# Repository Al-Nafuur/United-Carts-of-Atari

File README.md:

# Atari 2600 PlusCart

## Description
the Atari 2600 PlusCart ist based on Robin Edwards Unocart-2600 (https://github.com/robinhedwards/UnoCart-2600) and the extensions of Christian Speckner's (DirtyHairy) fork (https://github.com/DirtyHairy/UnoCart-2600). The PlusCart has no SD-Card, but an ESP8266 to connect to a local WiFi Network and the Internet.
The PlusCart downloads the ROM-files from an Server in the Internet called the "PlusStore". The way this is done is similar to the way the Unocart-2600 loads ROMs from the FAT filesystem on the SD-card, while the VCS is performing a waitroutine in his RAM.

## PlusROM
Additionally the PlusCart has one more interesting feature. It offers **internet access** to the ROM Developers, these functions are called "[PlusROM](http://pcart.firmaplus.de/pico/?PlusROM)". Examples for PlusROMs can be found in the [PlusROM-Hacks Repository](https://github.com/Al-Nafuur/PlusROM-Hacks) on Github.

## [Documentation](http://pcart.firmaplus.de/pico/)
More information and documentation can be found at the [PlusCart website](http://pcart.firmaplus.de/pico/)

Copyright:

(c) Firmaplus(+) Ltd.

Dipl.Ing.(FH) Wolfgang Stubig

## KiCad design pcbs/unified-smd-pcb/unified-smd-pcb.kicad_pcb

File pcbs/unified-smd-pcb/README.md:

Unified PlusCart UnoCart SMD PCB
===============

based on Randy Glenn's Unocart2600 PCB 
https://github.com/rglenn/unocart2600-pcb

migrated to KiCAD 6 and PlusCart WiFi module ESP8266 added by Wolfgang Stubig

Licensed under CERN OHL 1.2. See LICENSE.txt for more information.

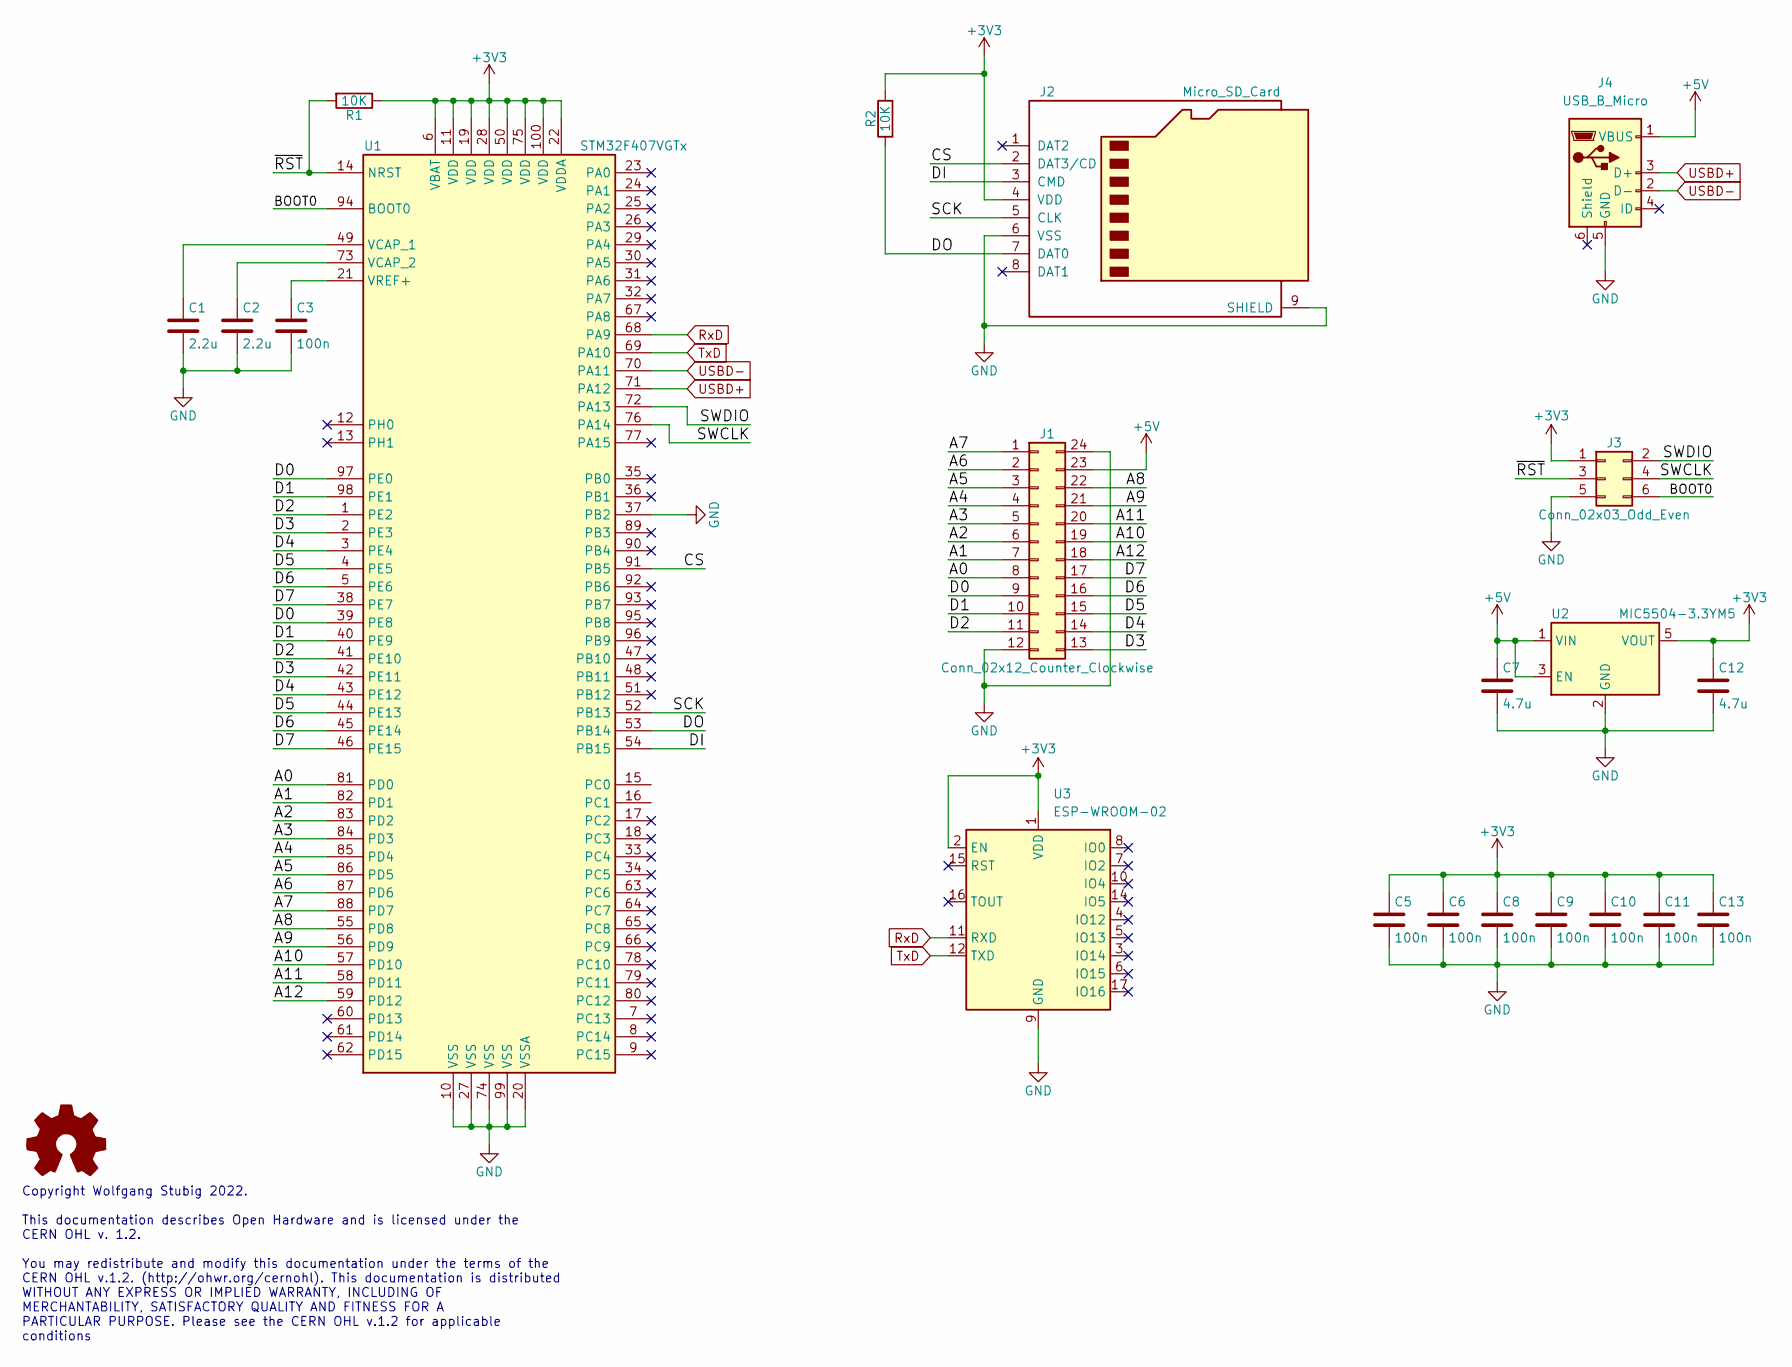
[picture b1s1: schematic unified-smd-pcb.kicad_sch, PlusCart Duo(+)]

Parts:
C1, C2: 2.2u; C_0603_1608Metric
C3, C5, C6, C8, C9, C10, C11, C13: 100n; C_0603_1608Metric
C7, C12: 4.7u; C_0805_2012Metric
J1: Conn_02x12_Counter_Clockwise; 2600-CARTRIDGE
J2: Micro_SD_Card; microSD_HRO_TF_01A
J3: Conn_02x03_Odd_Even; Tag-Connect_TC2030-IDC-NL_2x03_P1.27mm_Vertical
J4: USB_B_Micro; USB_Micro-B_Molex_47346-0001
R1, R2: 10K; R_0603_1608Metric
U1: STM32F407VGTx; LQFP-100_14x14mm_P0.5mm
U2: MIC5504-3.3YM5; SOT-23-5
U3: ESP-WROOM-02

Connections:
+3V3: C5.1, C6.1, C8.1, C9.1, C10.1, C11.1, C12.1, C13.1, J2.4 (VDD), J3.1, R1.1, R2.2, U1.6 (VBAT), U1.11 (VDD), U1.19 (VDD), U1.22 (VDDA), U1.28 (VDD), U1.50 (VDD), U1.75 (VDD), U1.100 (VDD), U2.5 (VOUT), U3.1 (VDD), U3.2 (EN)
+5V: C7.1, J1.23, J4.1 (VBUS), U2.1 (VIN), U2.3 (EN)
/A0: J1.8, U1.81 (PD0)
/A1: J1.7, U1.82 (PD1)
/A2: J1.6, U1.83 (PD2)
/A3: J1.5, U1.84 (PD3)
/A4: J1.4, U1.85 (PD4)
/A5: J1.3, U1.86 (PD5)
/A6: J1.2, U1.87 (PD6)
/A7: J1.1, U1.88 (PD7)
/A8: J1.22, U1.55 (PD8)
/A9: J1.21, U1.56 (PD9)
/A10: J1.19, U1.57 (PD10)
/A11: J1.20, U1.58 (PD11)
/A12: J1.18, U1.59 (PD12)
/BOOT0: J3.6, U1.94 (BOOT0)
/CS: J2.2 (DAT3/CD), U1.91 (PB5)
/D0: J1.9, U1.39 (PE8), U1.97 (PE0)
/D1: J1.10, U1.40 (PE9), U1.98 (PE1)
/D2: J1.11, U1.1 (PE2), U1.41 (PE10)
/D3: J1.13, U1.2 (PE3), U1.42 (PE11)
/D4: J1.14, U1.3 (PE4), U1.43 (PE12)
/D5: J1.15, U1.4 (PE5), U1.44 (PE13)
/D6: J1.16, U1.5 (PE6), U1.45 (PE14)
/D7: J1.17, U1.38 (PE7), U1.46 (PE15)
/DI: J2.3 (CMD), U1.54 (PB15)
/DO: J2.7 (DAT0), R2.1, U1.53 (PB14)
/SCK: J2.5 (CLK), U1.52 (PB13)
/SWCLK: J3.4, U1.76 (PA14)
/SWDIO: J3.2, U1.72 (PA13)
/~RST: J3.3, R1.2, U1.14 (NRST)
GND: C1.2, C2.2, C3.2, C5.2, C6.2, C7.2, C8.2, C9.2, C10.2, C11.2, C12.2, C13.2, J1.12, J1.24, J2.6 (VSS), J2.9 (SHIELD), J3.5, J4.5 (GND), U1.10 (VSS), U1.20 (VSSA), U1.27 (VSS), U1.37 (PB2), U1.74 (VSS), U1.99 (VSS), U2.2 (GND), U3.9 (GND), U3.13 (GND), U3.18 (GND), U3.19 (GND)
unnamed: C1.1, U1.49 (VCAP_1)
unnamed: C2.1, U1.73 (VCAP_2)
unnamed: C3.1, U1.21 (VREF+)
RxD: U1.68 (PA9), U3.11 (RXD)
TxD: U1.69 (PA10), U3.12 (TXD)
USBD+: J4.3 (D+), U1.71 (PA12)
USBD-: J4.2 (D-), U1.70 (PA11)

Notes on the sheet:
Copyright Wolfgang Stubig 2022. This documentation describes Open Hardware and is licensed under the CERN OHL v. 1.2. You may redistribute and modify this documentation under the terms of the CERN OHL v.1.2. (http://ohwr.org/cernohl). This documentation is distributed WITHOUT ANY EXPRESS OR IMPLIED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

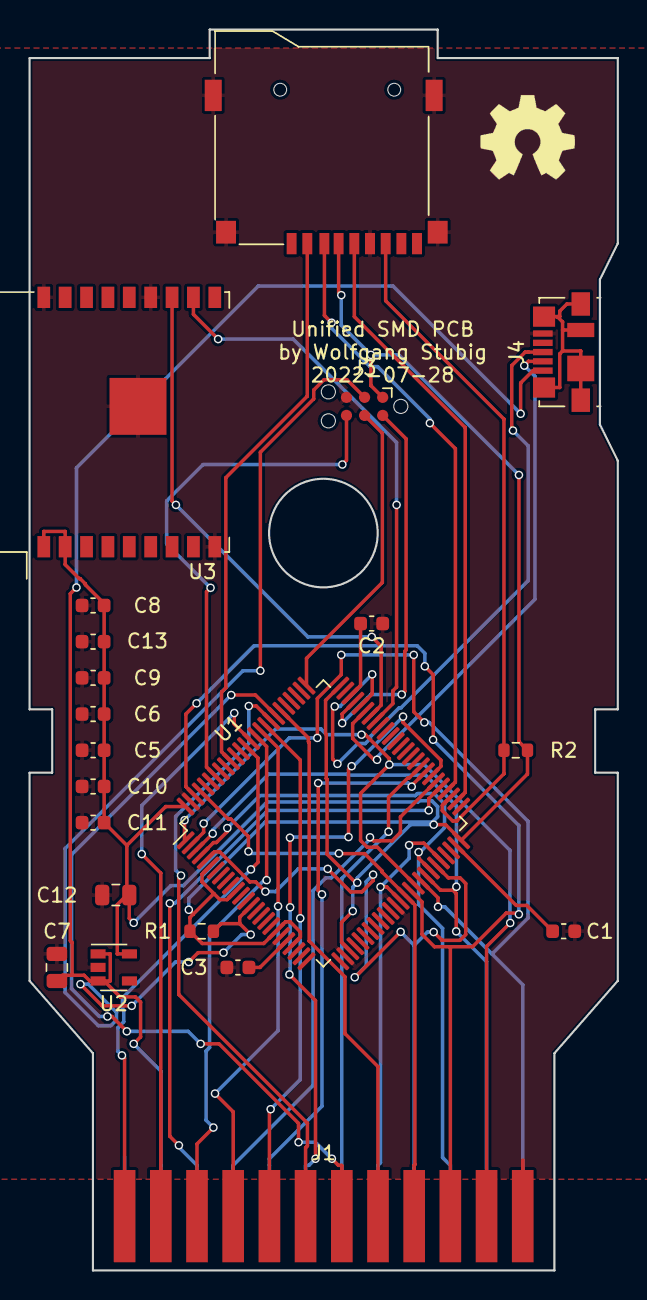
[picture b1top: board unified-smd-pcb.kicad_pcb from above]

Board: 2 copper layers, 41.3 x 87.1 mm, 21 parts (0 on the bottom side), 39 nets.

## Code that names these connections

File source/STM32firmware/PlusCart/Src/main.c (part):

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  GPIO_InitStruct.Pull = GPIO_NOPULL;
  HAL_GPIO_Init(GPIOC, &GPIO_InitStruct);
#elif HARDWARE_TYPE == UNOCART
  /*Configure GPIO pins : PE8 PE9 PE10 PE11
                           PE12 PE13 PE14 PE15 */
  GPIO_InitStruct.Pin = GPIO_PIN_8|GPIO_PIN_9|GPIO_PIN_10|GPIO_PIN_11
                          |GPIO_PIN_12|GPIO_PIN_13|GPIO_PIN_14|GPIO_PIN_15;
  GPIO_InitStruct.Mode = GPIO_MODE_INPUT;
  GPIO_InitStruct.Pull = GPIO_NOPULL;
  HAL_GPIO_Init(GPIOE, &GPIO_InitStruct);
#endif
  /*Configure GPIO pins : PD8 PD9 PD10 PD11
                           PD12 PD13 PD14 PD15
                           PD0 PD1 PD2 PD3
                           PD4 PD5 PD6 PD7 */
  GPIO_InitStruct.Pin = GPIO_PIN_8|GPIO_PIN_9|GPIO_PIN_10|GPIO_PIN_11
                          |GPIO_PIN_12|GPIO_PIN_13|GPIO_PIN_14|GPIO_PIN_15
                          |GPIO_PIN_0|GPIO_PIN_1|GPIO_PIN_2|GPIO_PIN_3
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
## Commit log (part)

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2020-01-10 store offline ROMs in flash memory
2020-01-12 Bugfix/Update DPC emulation
2020-01-30 Add reference to DirtyHairy's fork
2020-01-30 add detection for BF/BFSC and DF/DFSC
2020-01-30 placed (simulated) eeprom area in flash sector 1 add label ".flash0" for code in (boot-)sector 0
2020-01-30 prepare HTTP range requests for API, and cleanup
2020-01-31 Moved/reorganized flash related stuff to flash modul User settings in eeprom emulation flash sector 1 Bugfix for flashing ROM collections > 256 Kb Code cleanup
2020-01-31 new binaries for v0.11.0
2020-02-04 Message for ACE ROM unsupported
2020-02-04 Bugfix and reorganization for DF, DFSC, BF and BFSC
2020-02-06 tail only for ROMs larger than BUFFER_SIZE
2020-02-14 reworked esp8266 lib range requests wait for expected_size with 15s timeout, read Content-Lenght from response header, use Content-Length for menu loading also.
2020-02-20 version bump
2020-02-20 fixed bug in last chunk size calculation tweak pause between requests
2020-02-20 WiFi retry connect option startup tweaks moved EXT_TO_CART_TYPE_MAP from ccmram back to flash moved cart_base_type, CART_TYPE and EXT_TO_CART_TYPE_MAP to private
2020-02-25 PlusROM bugfixes by Thomas Jentzsch
2020-02-28 bugfixes Sadistroids by JTZ
2020-02-28 PAL color tweaks by JTZ
2020-03-01 Bugfix Supercharger multiload map request
2020-03-02 fallback to prevent empty Menu or Dir
2020-03-06 WPS (WiFi Protected Setup) Factory reset for ESP8266 auto detection and emulation for 6144 bytes Supercharger ROMs
2020-03-13 fix URI encode bug at Plus connect and Plus remove
2020-03-21 changed ASM Code for new PlusROM detection
2020-03-21 Version bump to v0.12.0
2020-03-21 use existing functions for BF and offline ROMs flash download.
2020-03-31 4 bytes optimization
2020-03-31 skip flashing user settings area
2020-04-04 code clean up
2020-04-05 new Binaries for v0.13.4
2020-04-08 changed download to flash check for offline ROMs in flash storage new function to erase flash storage
2020-04-08 new binaries for v0.13.6
2020-04-09 new binaries for v0.13.7
2020-04-27 Bugfix delete trailing 1 when scroll back from page 10 to 9
2020-04-27 New WiFi Manager Portal
2020-05-01 Search function in PlusCart start menu
2020-05-08 tweak API connect TCP timeout
2020-05-15 Detection for DPC+
2020-05-15 3E+ detection for ROM size <=64K and % 1K
2020-05-15 new binaries for version v0.14.6
2020-07-08 support for SB (SuperBanking)
2020-07-08 rearranged and merged emulation functions
2020-07-08 different color for directories in menu
2020-07-11 Online Combat PoC
2020-08-21 changed wording, dont use chunks for range parts
2020-08-27 new section for ROM BUFFER in RAM at 0x20000000
2020-08-28 I don't know why this byte has changed (ask DASM)
2020-08-28 DPC+ experimental support
2020-08-28 new binaries for v0.14.12
2020-08-31 bugfix for menu responses larger than 9999 bytes
2020-08-31 new binaries for version v0.14.13
2020-09-01 new binaries for v0.14.14
2020-09-08 Bugfix PlusROM backend connect
2020-09-08 version bump to v0.14.15
2020-09-11 new combat version (client and backend)
2020-09-11 switch to stdbool and user selectable font
2020-09-11 64 RAM pages for 3E+ and switch to stdbool
2020-09-12 use stdbool, bugfix eeprom emulation, tweak user_settings read/write
2020-09-17 fixed pointer to PlusROM backend definition
2020-09-20 merged new font code. Branch 'boo' can be discarded. Use this instead.
2020-09-21 Changed logo/spinner colour to white. Set titlebar font to hardwired TJZ
2020-09-21 font testbed now handles all fonts via switch (FONT) Note that these fonts are the MASTER definitions - change here first build and check on '2600/emulator. and then copy the font data to the firmwar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
2020-09-23 prelim to fixing/synching fonttestbed with cartridge_firmware - hand-dissasembled and commented firmware
2020-09-30 add asm code for Pitfall High Score Club
2020-10-03 add asm code for Barnstorming High Score Club
2020-10-05 some tweaks to the @ and glacier belle font
2020-10-05 Add Astroblast HighScore ASM code
2020-10-06 Add Turmoil HighScore ASM code
2020-10-08 removed hardwired local password. code cleanup. font mods.
2020-10-11 Add Demon Attack HighScore ASM code
2020-10-14 fixed keyboard for username/email entry in plusstore connect
2020-10-29 Add Pac-Man 4K HighScore ASM dev code
2020-10-30 add gitignore for build folders
2020-11-02 fixed flashing menu selection bar/line
2020-11-02 small fix for future reads without a break in firmware emulation function
2020-11-02 restored (temporarily) creators name in main menu statusbar
2020-11-02 binaries for new version
2020-11-05 fix for SuperCharger emulation not (always) waiting for address changes below 000
2020-11-05 rounder brackets in Glacier Belle font
2020-11-06 Working for the compiler (against my principles)
2020-11-06 New Pac-Man 4K HighScore ASM code
2020-11-10 nice "wifi not connected" character consistent with connected char
2020-11-11 Bugfix downloaded ROM size check, new message for "ROM Download Failed"
2020-11-17 Add Star Ship HighScore ASM dev code (NTSC only)
2020-11-18 rework of menu system
    * paging U/D/L/R function modified
    on a single page menu...
    UP will go to previous item on page
    DOWN will go to next item on page
    LEFT will go to top of page
    RIGHT will go to bottom of page
2020-11-19 Selectable text-line density, font-specific menu highlight centering
    1.
    There is a new "Setup/Set Line Spacing" menu option.
    This allows selection between...
    DENSE = 14 text lines in menu
    MEDIUM = 12 text lines in menu
    SPARSE = 10 text lines in menu
2020-11-26 More work on the line spacing and communication -> 2600
    * new ZP var 'lineCounter' counts lines in the kernel for use in menu navigation
    The easiest way seemed to be to just manage the variable in the kernel, such that
    at the end of every frame it has the correct number of lines on the menu/screen.
    This value is used when you press UP in menu navigation. If at the top already
    (line 0) then UP takes you to the previous page AND the last line on that page.
    COuld not use the #elements on page from online value, as that is incorrect for
2020-11-30 Checking default values for new (none initial) user_settings
2020-11-30 Min, max and default for user_settings
2020-12-02 Download offline ROMs with MAX_RANGE_SIZE http requests and small cleanup
2020-12-02 new Version for new backend API route with user/device settings
2020-12-02 (re)fixed the corrupt wifi character on page 1
    Code seems to have reverted somehow.
    I did a diff on a local backup and inserted the changes. All good.
2020-12-10 Bug Fix, allow "Z" and "z" in domain name for PlusROM detection
2020-12-10 DataFetcher copy tweaks
2020-12-16 removed const keyboard layout from RAM to flash sector 0
2020-12-30 Lots of changes to how menus work/operate.
    1. The menu code is essentially the same, but code is cleaner and simpler.
    2. The status message bar now...
    * displays the item selected, trimmed
    (prepended with ... to keep last part visible)
    * displays the item selected (e.g., "about.txt").
    3. Items now display instructions/info...
2020-12-31 Now truncates/shows right-side of ALL status message strings
    In the menu status string, now allows any string to be passed as status
    and the string will be displayed right-justified so that it fits in
    the avaialble space. The avialable space depends on #pages, etc... this
    is correctly calculated at display time to maximise use of status space
    The "..." has been changed to ".." to give an extra character for use
    BUGS
2020-12-31 Added dual-char "..." elipsis to all fonts
    Used in the start of the status-line if line is truncated.
2020-12-31 Tweaks to status line...
    * removed visualPath variable - now unused
    * squeezed in one more character before ellipsis used
2021-01-01 Fix for "/" truncation error in keyboard
2021-01-01 Add "System Info" and generic file/folder reads from API to the Setup menu
2021-01-01 code cleanup and entries renamed
2021-01-01 removed version and paging status types and paging_required flag
2021-01-02 Rewrites to save ROM/RAM space
    I've changed a few bits of code to be more efficient and save ROM.
    The character-array 'status_message' is now properly defined to not pad
    with extra characters. It no longer lives in .flash0 as I can't see how
    an array of this type can be placed there.
    In any case, ROM savings almost 1K. Most of the action is in the TV_Mode,
    Line_spacing and Font_style functions/code.
2021-01-02 "System Info" redesign
2021-01-08 optimisations + menu highlight line
    1. used sprintf in the "System Info" routine for string creation, as
    this uses less ROM
    2. Some modifications to the Glacier Belle font
    3. Fixed 1-pixel glitch on line 4 of menu (BG pixel, left edge)
2021-01-09 fixed wording in WiFi Manager Protal
2021-01-10 Init'd reflect for sprites in kernel. Minor font changes.
    1) Now initialises REFP0/P1 to 0 in kernel, so we won't see mirrored
    sprites. It doesn't hurt to do this, and may prevent issues with
    registers not being initialised.
    2) Some changes to the digits, slashes, apostrophe in Glacier Belle.
2021-01-10 adjust SSID and password parsing to new path length
2021-01-11 Fixed font display on selection menu
    1) Fonts were not displaying in their own font. Was due to an optimisation
    which just used user_settings.font. Now corrected.
2021-01-11 Renamed "Select WiFi Network" to "Scan for WiFi Access Points"
2021-01-12 changes to line 1419 should fix DPC exit, but it doesn't ! prevent boot init (1024 bytes of zero) for http_request_header, curPath and input_field compute max_romsize according to MCU
2021-01-13 removed warnings on DPC sound code. will it work?
2021-01-25 new Version v1.0.0 for Release
2021-02-02 Prelim alex_79's menu kernel
    First version using the new "flicker-free" menu.
    This should fix the flashing of P0 on those machines with odd spacing/glitches
2021-02-04 fixed UP in menu to go to last item on previous page
2021-02-04 Add SPI HAL Driver
2021-02-04 FatFs implemtation
2021-02-04 switches for hardware and periphery
2021-02-06 UnoCart GPIO fix, firmware update from SD-Card
2021-02-06 new major version number for reunited code base
2021-02-06 more SD-Card functions
2021-02-06 new Version "v2.0.0b"
2021-02-07 cleanup and extract
2021-02-07 New binaries for v1.1.0
2021-02-10 add periphery info to the client conf header
2021-02-24 always escape spaces in API HTTP requests receive status msg and path truncate from PlusStore API
2021-02-24 more generic keyboard always escape spaces in API HTTP requests receive status msg and path truncate from PlusStore API clean up status messages
2021-02-25 reset RIOT at start and after exit emulation
2021-03-02 Bugifx eeprom addressing
2021-03-04 fix for flash download of files smaller than MAX_RANGE_SIZE (32 KiB)
2021-03-05 Add new build folder names to gitignore
2021-03-08 Set default font to "Glacier Belle"
2021-03-11 strcasestr search with word boundary
2021-05-30 Changed clock timings for PlusROM functions
2021-06-05 New Binaries for version v2.1.0 release
2021-09-20 move PlusROM examples to own repository
2021-09-27 new binaries for version v2.2.0
2021-10-31 Fix compilation errors.
2022-01-26 More Parameters and comments added.
2022-02-01 language settings changed by IDE update
2022-02-01 downlad firmware images > 112 KiB
2022-06-09 Fix multiple esp8266_at_version build error.
2022-12-09 Set initial http range to 00000
2022-12-09 WIP DMA stream for data fetcher copy
2023-01-12 Add E78K detection
2023-01-12 new version v2.3.15
2023-01-25 DPC+ ELF wrapper test initial commit
2023-02-20 Switch back to HSI
2023-02-20 new binaries for v2.3.16
2023-02-20 new version v2.3.17
2023-10-10 Run emulate_standard_cartridge() from RAM to prevent Flash Cache misses from causing game glitches and crashes.
2024-09-01 Fix for toolchain sysmem?
2024-09-01 ZacharyScolaro Supercharger bios fix.
2024-11-08 Add API-Host to user settings
2024-11-08 -Add API host
2024-11-08 -Add FA2 -Add API host
2024-11-08 New binaries for version v2.3.24
2025-01-14 cleanup and fix PlusROM exit
2025-01-14 New version v2.3.28
2025-03-29 Fixed 2600 bootstrap Fixed page icon location Fixed missing page numbers Fixed pagination Fixed extra dots after some file names Fixed background color of previously selected items Increased file nam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
2025-05-13 Fix links
2025-10-18 corrected filename of included in esp8266.c
    the file is named "esp8266_AT_WiFiManager.h" but the file included was
    "esp8266_AT_WifiManager.h"
    the lower-case 'f' in WiFi is a problem for UNIX like systems where
    filenames are case sensitive
2025-11-08 Added VcsWrite4()
2025-11-12 fix: moved NOP to allow more time after reading value on databus
2025-11-13 fix: adding vcsNop2 *after* SnoopDataBus
2025-11-13 feature sync: ColorLookup isn't supported in CC firmware

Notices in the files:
source/STM32firmware/PlusCart/Src/main.c:
(c) 2019 Wolfgang Stubig (Al_Nafuur)
This program is free software: you can redistribute it and/or modify
it under the terms of the GNU General Public License as published by
the Free Software Foundation, either version 3 of the License, or
(at your option) any later version.
(C) COPYRIGHT STMicroelectronics *****END OF FILE
